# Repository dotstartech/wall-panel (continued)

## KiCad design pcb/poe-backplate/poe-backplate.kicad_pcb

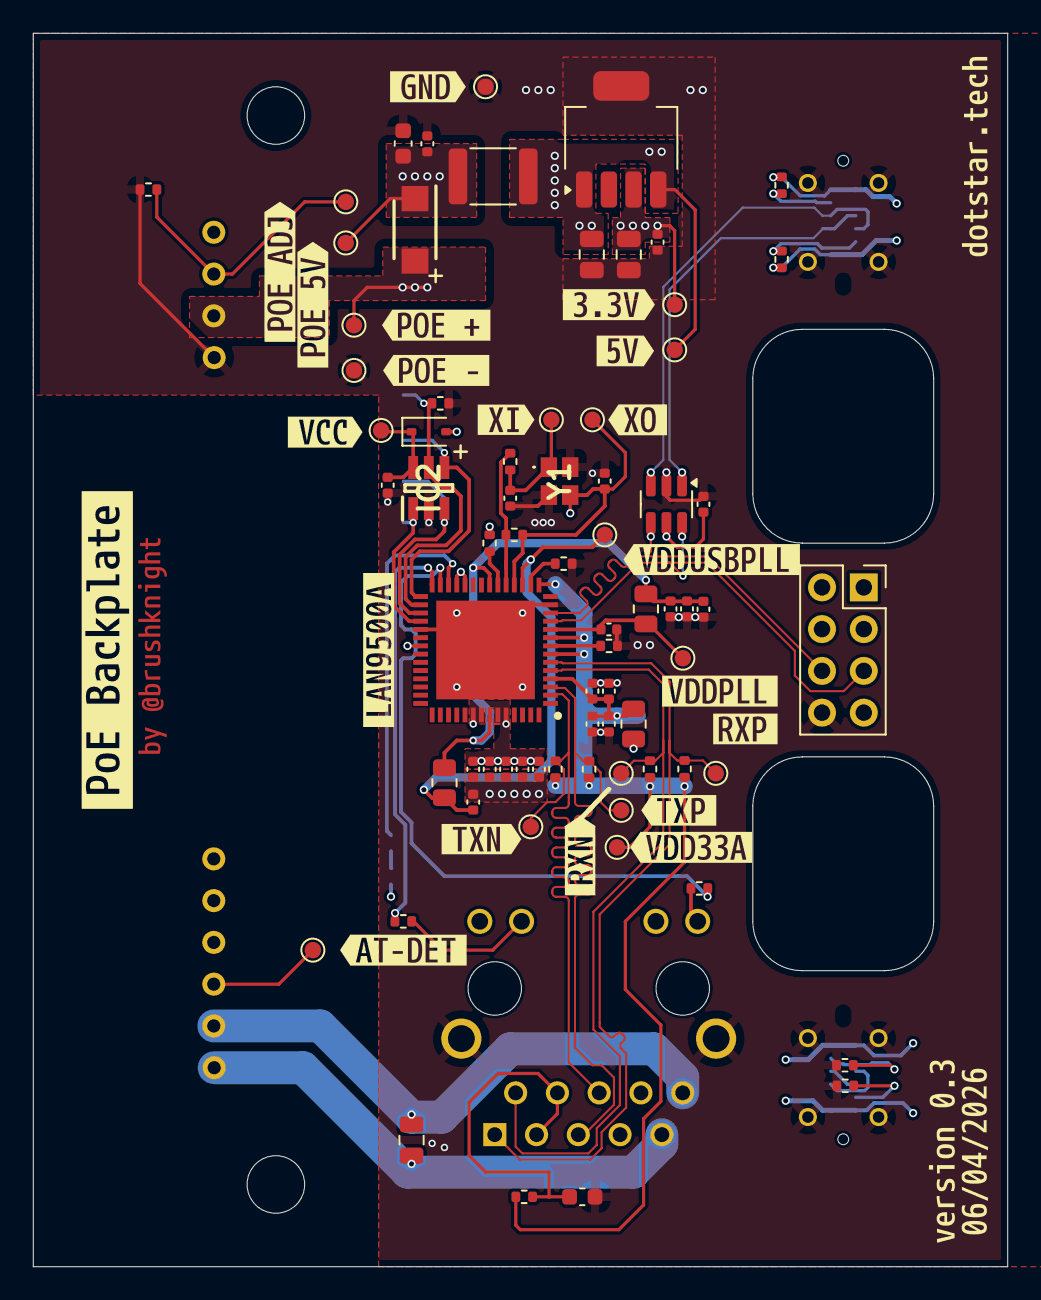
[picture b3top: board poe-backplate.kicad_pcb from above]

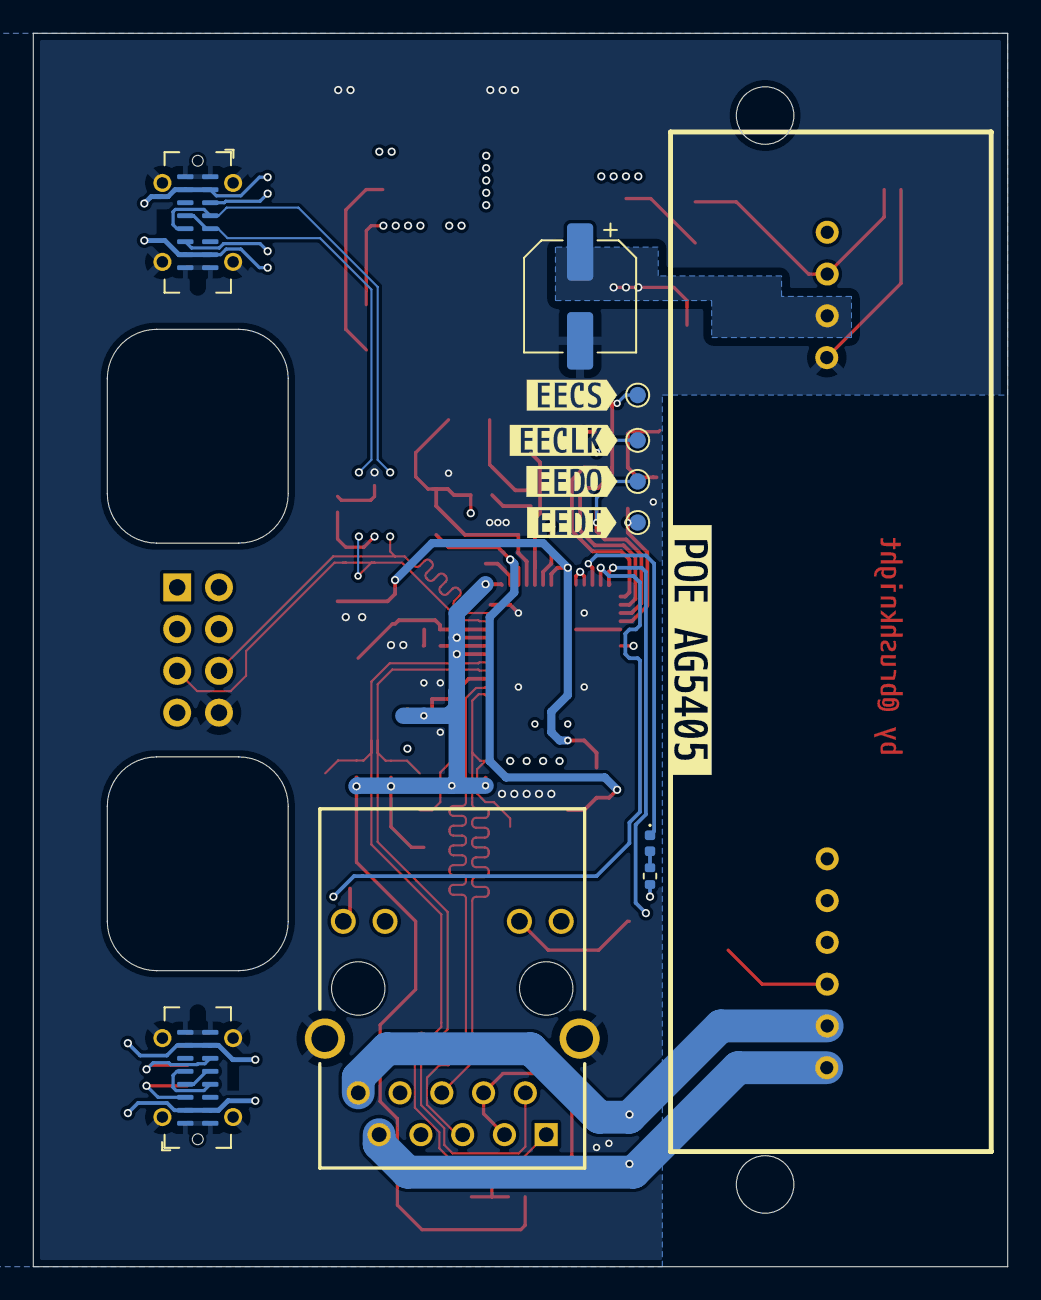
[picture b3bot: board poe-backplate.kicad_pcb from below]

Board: 6 copper layers, 59.2 x 75.0 mm, 113 parts (16 on the bottom side), 45 nets.

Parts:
C1, C2, C3, C4, C5, C6, C7, C8, C9, C11, C12, C13, C14, C16, C20, C22, C26: 100nF; C_0402_1005Metric
C10: 1uF; C_0402_1005Metric
C15, C18: 24pF; C_0402_1005Metric
C17, C19: 1uF; C_0805_2012Metric
C21: 1uF; C_0603_1608Metric
C23: 22nF; C_0603_1608Metric
C24: 10nF; C_0805_2012Metric
C25: 470µF; CP_Elec_6.3x7.7
D1: GREEN; LED_0402_1005Metric
D2: B0540WS; D_SOD-323
D3: SS54F; SODFL4626X120N
FB1, FB2, FB3: BLM21PG221SN1D; R_0805_2012Metric
FB4: CBM453215U101T; R_1812_4532Metric
IC1: LAN9500A-ABZJ; QFN50P800X800X100-57N-D
IC2: 93LC66AT-I_OT; SOT95P270X145-6N
J3, J4: USB_C_Receptacle_USB2.0_14P; USB_C_Receptacle_G-Switch_GT-USB-7051x
J5: Conn_02x04_Counter_Clockwise; PinSocket_2x04_P2.54mm_Vertical
POE1: AG5405
R1, R2: 12K; R_0402_1005Metric
R3, R5: 0; R_0402_1005Metric
R4: 1M; R_0402_1005Metric
R6, R12, R13: 3.3K; R_0402_1005Metric
R7: 10K; R_0402_1005Metric
R8, R10: 56K; R_0402_1005Metric
R9, R11: 5.1K; R_0402_1005Metric
R14: 10; R_0402_1005Metric
R15, R16, R17, R18: 49.9; R_0402_1005Metric
R19: 50K; R_0402_1005Metric
TP1, TP2, TP3, TP4, TP5, TP6, TP7, TP8, TP9, TP10, TP11, TP12, TP13, TP14, TP15, TP16, TP17, TP18, TP19, TP20, TP21, TP22: TestPoint; TestPoint_Pad_D1.0mm
U1: LP38693MP-3.3; SOT-223-5
U2: HY931147C
U5: USBLC6-2SC6; SOT-23-6
Y1: ECS-250-18-36B2-CTY-TR; ECS2501836B2CTYTR
kibuzzard-68D6D404: G***; kibuzzard-68D6D404
kibuzzard-68D6D564: G***; kibuzzard-68D6D564
kibuzzard-68DA6D8B: G***; kibuzzard-68DA6D8B
kibuzzard-68DA50C8: G***; kibuzzard-68DA50C8
kibuzzard-68DA50CF: G***; kibuzzard-68DA50CF
kibuzzard-68DA50D5: G***; kibuzzard-68DA50D5
kibuzzard-68DA50DD: G***; kibuzzard-68DA50DD
kibuzzard-68DA54A3: G***; kibuzzard-68DA54A3
kibuzzard-68DA512A: G***; kibuzzard-68DA512A
kibuzzard-68DA5225: G***; kibuzzard-68DA5225
kibuzzard-68DA5440: G***; kibuzzard-68DA5440
kibuzzard-68DA5448: G***; kibuzzard-68DA5448
kibuzzard-68DA5505: G***; kibuzzard-68DA5505
kibuzzard-68DAA144: G***; kibuzzard-68DAA144
kibuzzard-69D3A52E: G***; kibuzzard-69D3A52E
kibuzzard-69D3A526: G***; kibuzzard-69D3A526
kibuzzard-697B6E2E: G***; kibuzzard-697B6E2E
kibuzzard-697B6E24: G***; kibuzzard-697B6E24
kibuzzard-697BD4F1: G***; kibuzzard-697BD4F1
kibuzzard-697F85B0: G***; kibuzzard-697F85B0
kibuzzard-697F855F: G***; kibuzzard-697F855F
kibuzzard-697F858D: G***; kibuzzard-697F858D
kibuzzard-697F8524: G***; kibuzzard-697F8524
kibuzzard-697F8566: G***; kibuzzard-697F8566
kibuzzard-6978AB6C: G***; kibuzzard-6978AB6C
kibuzzard-6978AB9F: G***; kibuzzard-6978AB9F
kibuzzard-6978AB59: G***; kibuzzard-6978AB59
kibuzzard-6985C4FD: G***; kibuzzard-6985C4FD
kibuzzard-6985C516: G***; kibuzzard-6985C516

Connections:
+3.3V: C1.2, C2.2, C4.2, C6.2, C8.2, C19.2, C20.2, D2.2 (A), FB1.1, IC1.24 (NRESET), IC1.25 (VDD33IO_1), IC1.35 (VDD33IO_2), IC1.48 (VDD33IO_3), IC1.49 (TEST1), IC1.51 (VDD33IO_4), IC1.52 (VDD33IO_5), R3.1, R6.2, TP13.1, U1.3 (OUT), U2.P$11 (Y+), U2.P$13 (G+)
+5V: C17.2, C26.2, FB4.2, J3.A4 (VBUS), J3.A9 (VBUS), J3.B4 (VBUS), J3.B9 (VBUS), J5.7, R8.2, R10.2, TP12.1, U1.1 (EN), U1.4 (IN), U5.5 (VBUS)
/PoE/ETH1_LEDG: IC1.27 (NLNKA_LED/GPIO9), R12.2
/PoE/ETH1_LEDY: IC1.28 (NSPD_LED/GPIO10), R13.2
/PoE/POE_5V: C21.1, C22.1, D3.1 (K), FB4.1, J4.A4 (VBUS), J4.A9 (VBUS), J4.B4 (VBUS), J4.B9 (VBUS), TP10.1
/PoE/RXN: IC1.5 (RXN), R15.2, TP21.1, U2.P$2 (RX-)
/PoE/RXP: IC1.6 (RXP), R16.2, TP22.1, U2.P$1 (RX+)
/PoE/TXN: IC1.2 (TXN), R17.2, TP19.1, U2.P$6 (TX-)
/PoE/TXP: IC1.3 (TXP), R18.2, TP20.1, U2.P$5 (TX+)
/PoE/VDD33A: C3.2, C5.2, C7.2, C9.2, FB1.2, IC1.4 (VDD33A_1), IC1.7 (NC_1), IC1.9 (VDD33A_2), IC1.15 (VDD33A_3), R14.1, R15.1, R16.1, R17.1, R18.1, TP16.1
/USB to Ethernet/CRYSTAL_XI: C18.2, IC1.18 (XI), R4.2, TP14.1, Y1.3 (OUT/IN)
/USB to Ethernet/CRYSTAL_XO: IC1.19 (XO), R4.1, R5.1
/USB to Ethernet/EECLK_GPIO3: IC1.29 (EECLK/PWR_SEL), IC2.4 (CLK), TP5.1
/USB to Ethernet/EECS_GPIO0: IC1.30 (EECS), IC2.5 (CS), R7.1, TP4.1
/USB to Ethernet/EEDI_GPIO1: IC1.32 (EEDI), IC2.1 (DO), TP2.1
/USB to Ethernet/EEDO_GPIO2: IC1.31 (EEDO/AUTOMDIX_EN), IC2.3 (DI), TP3.1
/USB to Ethernet/ETH1_LED_FDX: D1.1 (K), IC1.26 (NFDX_LED/GPIO8)
/USB to Ethernet/USBDN: IC1.11 (USBDM), J5.5, U5.6 (I/O1)
/USB to Ethernet/USBDP: IC1.12 (USBDP), J5.6, U5.4 (I/O2)
/USB to Ethernet/USB_D+: J3.A6 (D+), J3.B6 (D+), U5.3 (I/O2)
/USB to Ethernet/USB_D-: J3.A7 (D-), J3.B7 (D-), U5.1 (I/O1)
/USB to Ethernet/VDDCORE: C10.2, C11.2, C12.2, FB2.1, FB3.1, IC1.21 (VDDCORE_1), IC1.50 (VDDCORE_2)
/USB to Ethernet/VDDPLL: C14.2, FB3.2, IC1.10 (VDDPLL), TP18.1
/USB to Ethernet/VDDUSBPLL: C13.2, FB2.2, IC1.17 (VDDUSBPLL), TP17.1
GND: C1.1, C2.1, C3.1, C4.1, C5.1, C6.1, C7.1, C8.1, C9.1, C10.1, C11.1, C12.1, C13.1, C14.1, C15.1, C16.1, C17.1, C18.1, C19.1, C20.1, C21.2, C22.2, C23.2, C25.2, C26.1, IC1.13 (TEST2), IC1.33 (TEST3), IC1.57 (VSS), IC2.2 (VSS), J3.A1 (GND), J3.A12 (GND), J3.B1 (GND), J3.B12 (GND), J3.S1 (SHIELD), J4.A1 (GND), J4.A12 (GND), J4.B1 (GND), J4.B12 (GND), J4.S1 (SHIELD), J5.8, POE1.7 (-VDC), R1.1, R2.1, R7.2, R9.2, R11.2, R19.2, TP1.1, TP8.1, U1.5 (GND), U2.GND1, U2.GND2, U5.2 (GND), Y1.2 (GND_1), Y1.4 (GND_2)
unnamed: D1.2 (A), R6.1
unnamed: C16.2, D2.1 (K), IC2.6 (VCC), TP6.1
unnamed: C25.1, D3.2 (A), POE1.8 (+VDC_), TP9.1
unnamed: IC1.8 (EXRES), R1.2
unnamed: IC1.16 (USBRBIAS), R2.2
unnamed: IC1.20 (VBUS_DET), R3.2
unnamed: J3.A5 (CC1), R8.1
unnamed: J3.B5 (CC2), R10.1
unnamed: J4.A5 (CC1), R9.1
unnamed: J4.B5 (CC2), R11.1
unnamed: J4.A6 (D+), J4.B6 (D+)
unnamed: J4.A7 (D-), J4.B7 (D-)
unnamed: POE1.9 (ADJ), R19.1, TP7.1
unnamed: POE1.3 (AT-DET), TP11.1
unnamed: C24.1, POE1.1 (VIN+), U2.P$9 (V+)
unnamed: C24.2, POE1.2 (VIN-), U2.P$10 (V-)
unnamed: R12.1, U2.P$14 (G-)
unnamed: C23.1, R14.2, U2.P$3 (RXCT), U2.P$4 (TXCT)
unnamed: R13.1, U2.P$12 (Y-)
unnamed: C15.2, R5.2, TP15.1, Y1.1 (IN/OUT)

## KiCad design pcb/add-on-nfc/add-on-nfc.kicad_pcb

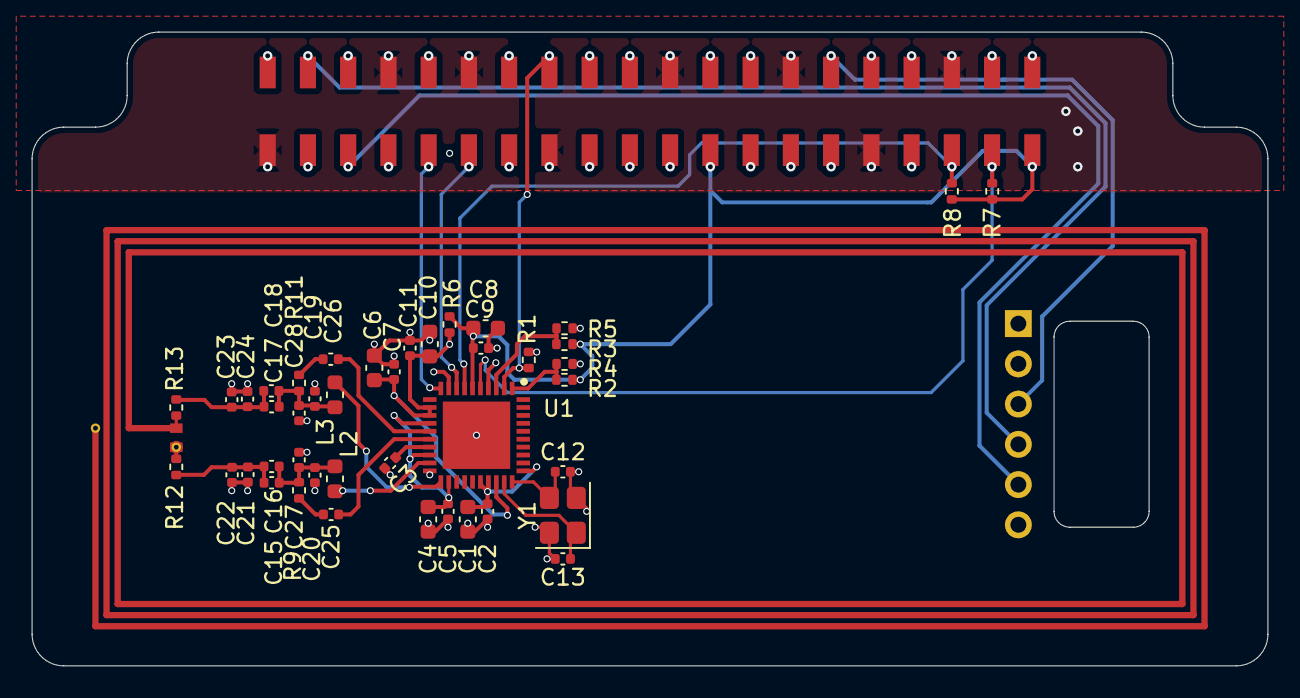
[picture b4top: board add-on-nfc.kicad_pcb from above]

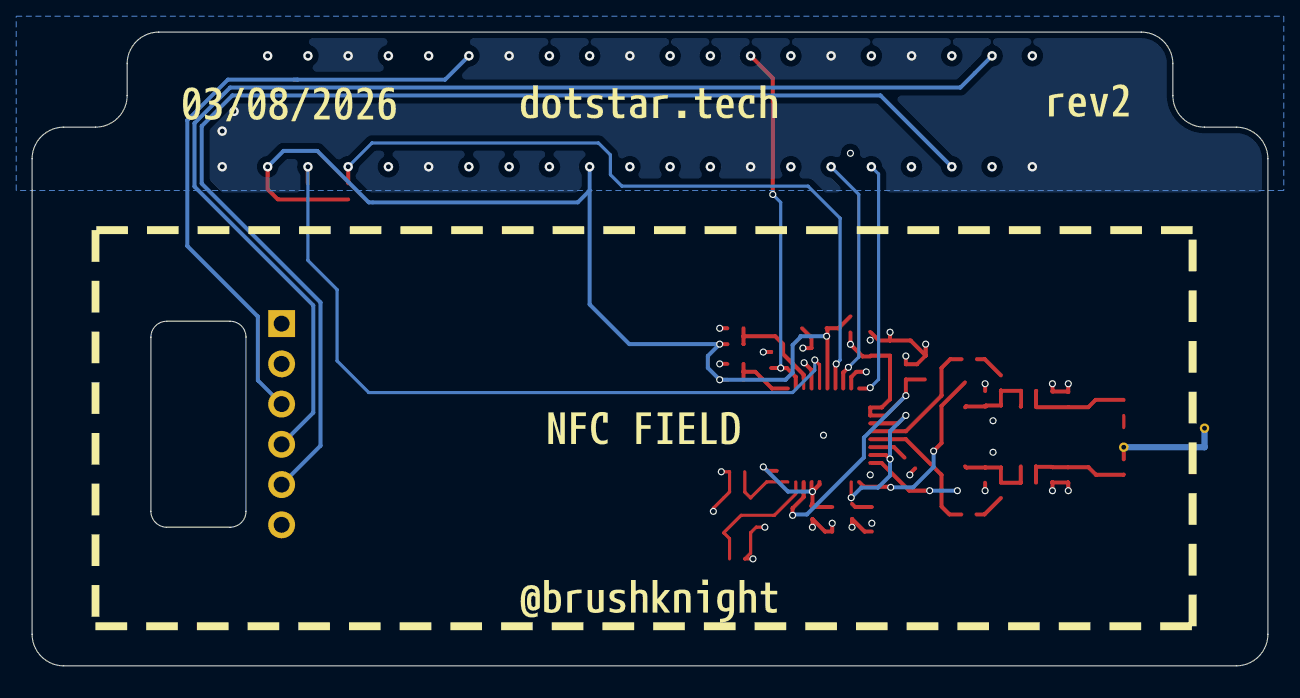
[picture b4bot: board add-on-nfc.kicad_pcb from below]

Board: 4 copper layers, 78.0 x 40.0 mm, 51 parts (5 on the bottom side), 30 nets.

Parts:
AE1: NFC_ANT_70x25_N3
C1, C4, C6, C8, C10: 10uF; C_0603_1608Metric
C2, C3, C5, C7, C9, C11: 100nF; C_0402_1005Metric
C12, C13: 15pF; C_0402_1005Metric
C15, C18: NC; C_0402_1005Metric
C16, C17: 82pF; C_0402_1005Metric
C19, C20: 270pF; C_0402_1005Metric
C21, C24: 150pF; C_0402_1005Metric
C22, C23: 68pF; C_0402_1005Metric
C25, C26: 1nF; C_0402_1005Metric
C27, C28: 56pF; C_0402_1005Metric
J5: Mic Adafruit; SPH0645LM4H
J10: PZ254-2-20-WS; PM254-2-20-WS-8.5
L2, L3: 160nH; L_0603_1608Metric
R1: 10K; R_0402_1005Metric
R2, R3: 10K/NC; R_0402_1005Metric
R4, R5: 100K; R_0402_1005Metric
R6: 0; R_0402_1005Metric
R7, R8: 4.7K/NC; R_0402_1005Metric
R9, R11: 2.2K; R_0402_1005Metric
R12, R13: 1.3K; R_0402_1005Metric
U1: PN7160A1HN_C100E; QFN50P600X600X100-41N-D
Y1: Crystal_GND24; Crystal_SMD_3225-4Pin_3.2x2.5mm
kibuzzard-6A72FB9B: G***; kibuzzard-6A72FB9B
kibuzzard-6A7047E1: G***; kibuzzard-6A7047E1
kibuzzard-6A7047FA: G***; kibuzzard-6A7047FA
kibuzzard-6A70481C: G***; kibuzzard-6A70481C
kibuzzard-6A70487D: G***; kibuzzard-6A70487D

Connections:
+3.3V: C8.1, C9.1, J5.1, J10.23, J10.39, R2.1, R3.1, R6.1, R7.2, R8.2, U1.6 (VDD_1)
+5V: C6.1, C7.1, C10.1, C11.1, J10.38, J10.40, R6.2, U1.12 (VBAT2), U1.13 (VDD(UP)), U1.28 (VBAT)
/ADDR0/NSS: R2.2, R4.2, U1.1 (I2C_ADR0/SPI_NSS)
/ADDR1/MOSI: R3.2, R5.2, U1.3 (I2C_ADR1/SPI_MOSI)
/DWL_REQ: J10.16, R1.2, U1.2 (DWL_REQ)
/GPIO2: J10.37, R7.1, U1.5 (I2C_SDA/SPI_MISO)
/GPIO3: J10.35, R8.1, U1.7 (I2C_SCL/SPI_SCK)
/GPIO5: J10.11, U1.8 (IRQ)
/GPIO6: J10.9, U1.10 (VEN)
/GPIO18: J5.3, J10.30
/GPIO19: J5.5, J10.5
/GPIO20: J5.4, J10.4
/RXN: C26.1, U1.15 (RXN)
/RXP: C25.1, U1.16 (RXP)
/TX1: L3.1, U1.21 (TX1)
/TX2: L2.1, U1.19 (TX2)
GND: C1.2, C2.2, C3.2, C4.2, C5.2, C6.2, C7.2, C8.2, C9.2, C10.2, C11.2, C12.2, C13.2, C19.2, C20.1, C21.1, C22.1, C23.2, C24.2, C27.1, C28.2, J5.2, J10.1, J10.8, J10.12, J10.15, J10.22, J10.28, J10.31, J10.36, R1.1, R4.1, R5.1, U1.4 (VSS_1), U1.9 (VSS(A)), U1.20 (VSS(TX)), U1.41 (VSS_2), Y1.2 (G), Y1.4 (G)
unnamed: AE1.1 (ANT+), R12.2
unnamed: AE1.2 (ANT-), R13.2
unnamed: C15.1, C16.1, C20.2, C27.2, L2.2, R9.1
unnamed: C15.2, C16.2, C21.2, C22.2, R12.1
unnamed: C17.1, C18.1, C19.1, C28.1, L3.2, R11.2
unnamed: C17.2, C18.2, C23.1, C24.1, R13.1
unnamed: C25.2, R9.2
unnamed: C26.2, R11.1
unnamed: C12.1, U1.30 (NFC_CLK_XTAL1), Y1.3
unnamed: C4.1, C5.1, U1.14 (VDD(TX)), U1.18 (TVDD_IN), U1.22 (VDD_IN2)
unnamed: C1.1, C2.1, U1.26 (VDD(A)), U1.27 (VDD_2), U1.31 (VDD(D))
unnamed: C3.1, U1.17 (VDD(VMID))
unnamed: C13.1, U1.29 (XTAL2), Y1.1

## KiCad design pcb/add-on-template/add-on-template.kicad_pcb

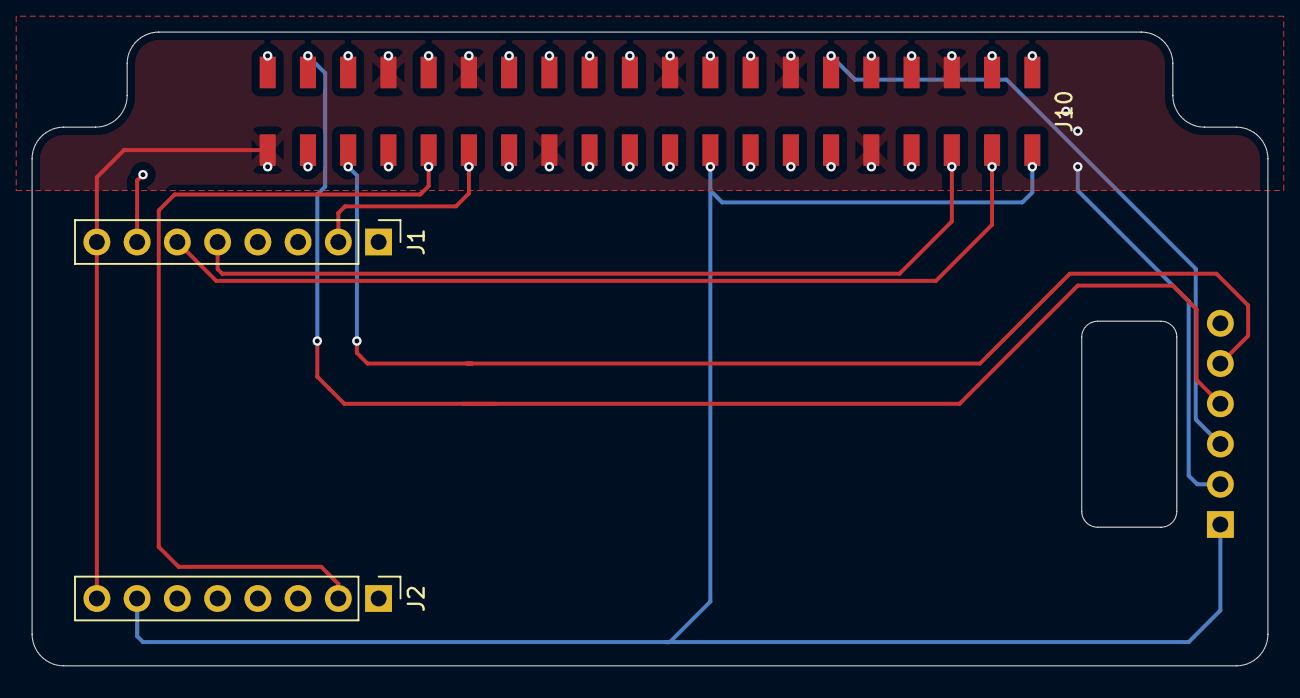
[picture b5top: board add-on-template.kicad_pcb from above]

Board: 4 copper layers, 78.0 x 40.0 mm, 4 parts (0 on the bottom side), 10 nets.

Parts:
J1: Left, i2c; PinHeader_1x08_P2.54mm_Vertical
J2: Right, 3v; PinHeader_1x08_P2.54mm_Vertical
J5: Mic Adafruit; SPH0645LM4H
J10: PZ254-2-20-WS; PM254-2-20-WS-8.5

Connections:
+3.3V: J2.7, J5.1, J10.23, J10.39
+5V: J1.7, J10.38, J10.40
/GPIO2: J1.6, J10.37
/GPIO3: J1.5, J10.35
/GPIO5: J1.2, J10.11
/GPIO6: J2.2, J10.9
/GPIO18: J5.3, J10.30
/GPIO19: J5.5, J10.5
/GPIO20: J5.4, J10.4
GND: J1.8, J2.8, J5.2, J10.1, J10.8, J10.12, J10.15, J10.22, J10.28, J10.31, J10.36

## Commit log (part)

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2026-01-09 wall panel v0.2
2026-01-09 added cad files
2026-01-09 updated docs
2026-01-09 Added CERN OHL
2026-01-09 Updated license from CERN-OHL-P to CERN-OHL-W
2026-02-05 wall panel v0.3
2026-02-06 added poe backplate v0.2
